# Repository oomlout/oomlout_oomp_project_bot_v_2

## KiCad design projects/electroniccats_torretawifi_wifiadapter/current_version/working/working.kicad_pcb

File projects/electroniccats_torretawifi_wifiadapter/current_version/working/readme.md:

# torretawifi
 
## summary 
* id: electroniccats_torretawifi_wifiadapter
* user: electroniccats
* name: torretawifi
* board: wifiadapter
* repo: https://github.com/ElectronicCats/TorretaWiFi
* src_file_repo_kicad_pcb: ADAPTADORESP/WiFiadapter.kicad_pcb
* src_file_repo_kicad_pcb_link: https://github.com/ElectronicCats/TorretaWiFi/tree/master/ADAPTADORESP/WiFiadapter.kicad_pcb

* src_file_repo_sch: ADAPTADORESP/WiFiadapter.sch
* src_file_repo_sch_link: https://github.com/ElectronicCats/TorretaWiFi/tree/master/ADAPTADORESP/WiFiadapter.sch
* full details link: https://github.com/oomlout/oomlout_oomp_project_bot_v_2/tree/main/projects/electroniccats_torretawifi_wifiadapter/current_version/working

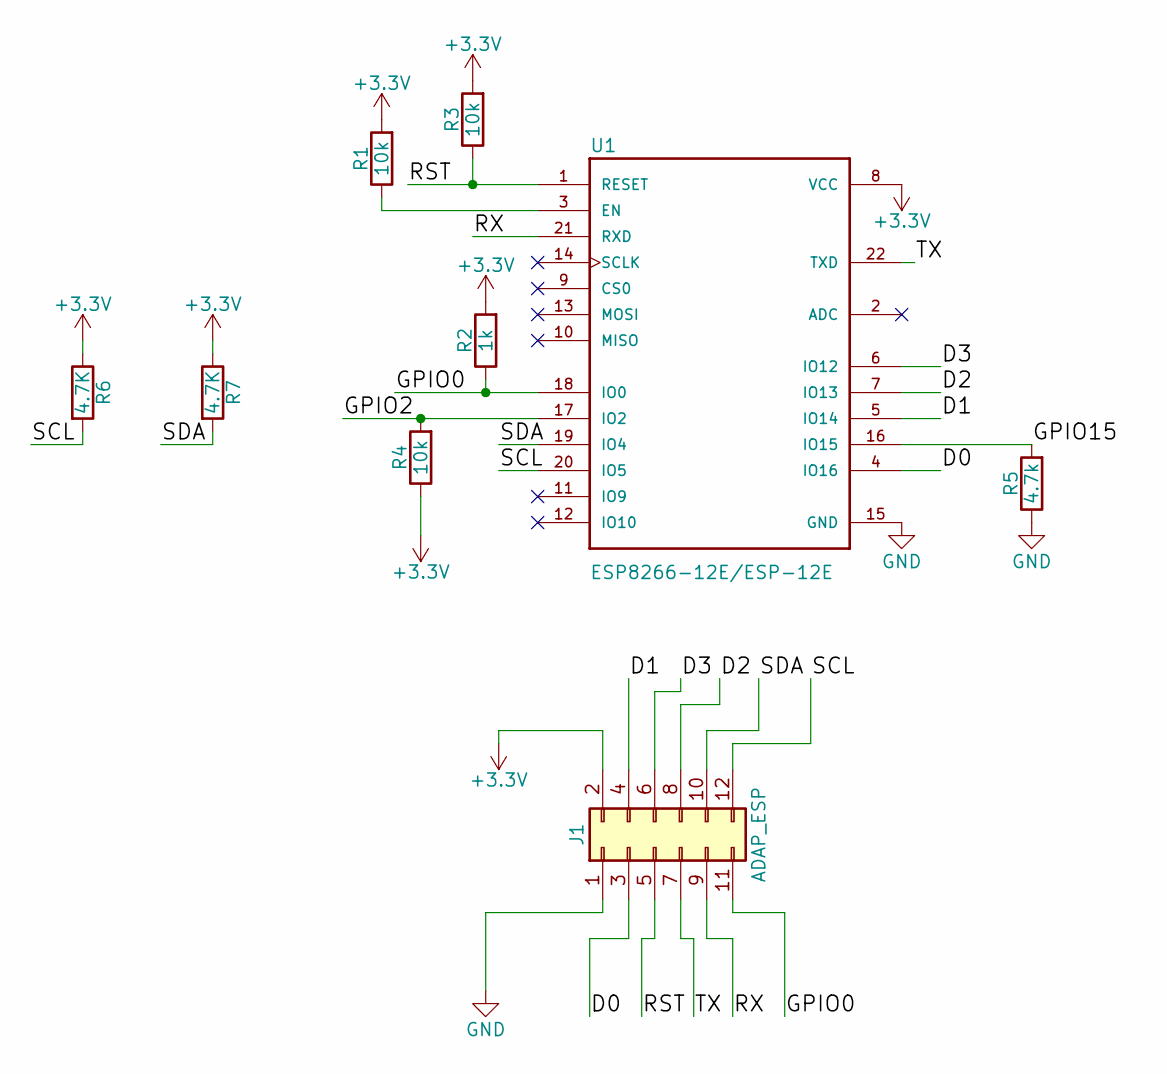
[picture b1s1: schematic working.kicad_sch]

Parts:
J1: ADAP_ESP; Pin_Header_Straight_2x06_Pitch2.54mm
R1, R3, R4: 10k; R_0805_HandSoldering
R2: 1k; R_0805_HandSoldering
R5: 4.7k; R_0805_HandSoldering
R6, R7: 4.7K; R_0805_HandSoldering
U1: ESP8266-12E/ESP-12E; XCVR_ESP8266-12E%2fESP-12E

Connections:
+3V3: J1.2, R1.2, R2.2, R3.2, R4.1, R6.1, R7.1, U1.8 (VCC)
/D0: J1.3, U1.4 (IO16)
/D1: J1.4, U1.5 (IO14)
/D2: J1.8, U1.7 (IO13)
/D3: J1.6, U1.6 (IO12)
/GPIO0: J1.11, R2.1, U1.18 (IO0)
/GPIO2: R4.2, U1.17 (IO2)
/GPIO15: R5.2, U1.16 (IO15)
/RST: J1.5, R3.1, U1.1 (RESET)
/RX: J1.9, U1.21 (RXD)
/SCL: J1.12, R6.2, U1.20 (IO5)
/SDA: J1.10, R7.2, U1.19 (IO4)
/TX: J1.7, U1.22 (TXD)
GND: J1.1, R5.1, U1.15 (GND)
unnamed: R1.1, U1.3 (EN)

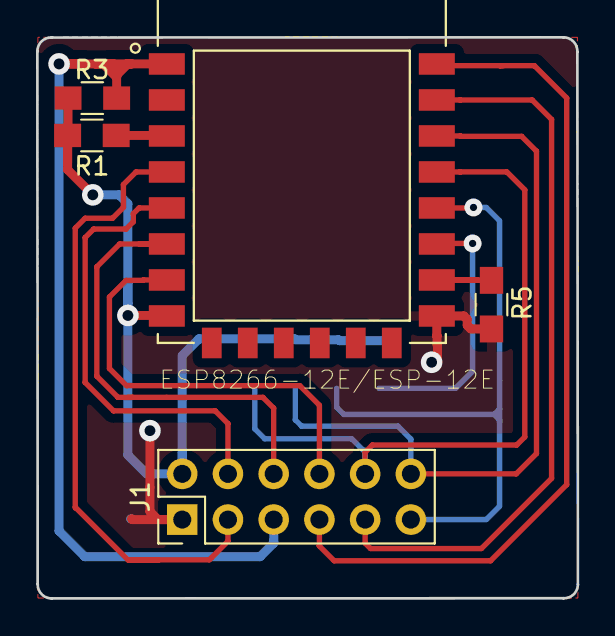
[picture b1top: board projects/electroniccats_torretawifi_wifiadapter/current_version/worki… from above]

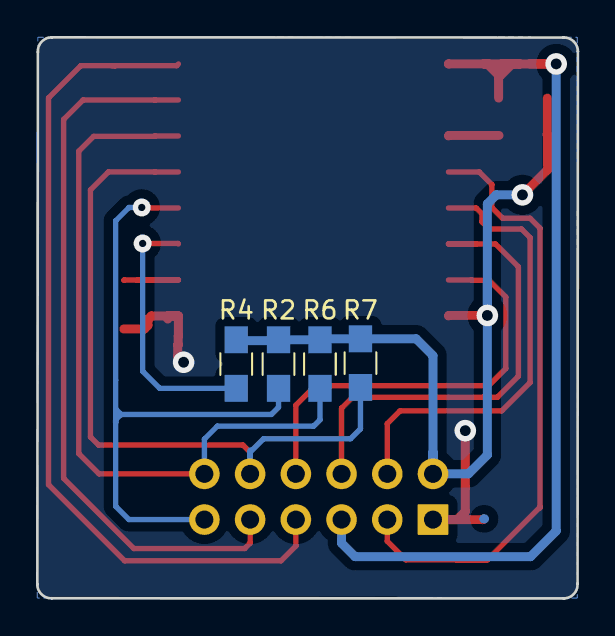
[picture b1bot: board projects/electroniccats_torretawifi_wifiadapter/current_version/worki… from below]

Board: 2 copper layers, 30.0 x 31.2 mm, 9 parts (4 on the bottom side), 15 nets.

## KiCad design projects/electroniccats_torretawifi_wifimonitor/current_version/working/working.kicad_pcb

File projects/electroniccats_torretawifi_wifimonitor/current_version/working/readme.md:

# torretawifi
 
## summary 
* id: electroniccats_torretawifi_wifimonitor
* user: electroniccats
* name: torretawifi
* board: wifimonitor
* repo: https://github.com/ElectronicCats/TorretaWiFi
* src_file_repo_kicad_pcb: Hardware/WiFiMonitor.kicad_pcb
* src_file_repo_kicad_pcb_link: https://github.com/ElectronicCats/TorretaWiFi/tree/master/Hardware/WiFiMonitor.kicad_pcb

* src_file_repo_sch: Hardware/WiFiMonitor.sch
* src_file_repo_sch_link: https://github.com/ElectronicCats/TorretaWiFi/tree/master/Hardware/WiFiMonitor.sch
* full details link: https://github.com/oomlout/oomlout_oomp_project_bot_v_2/tree/main/projects/electroniccats_torretawifi_wifimonitor/current_version/working

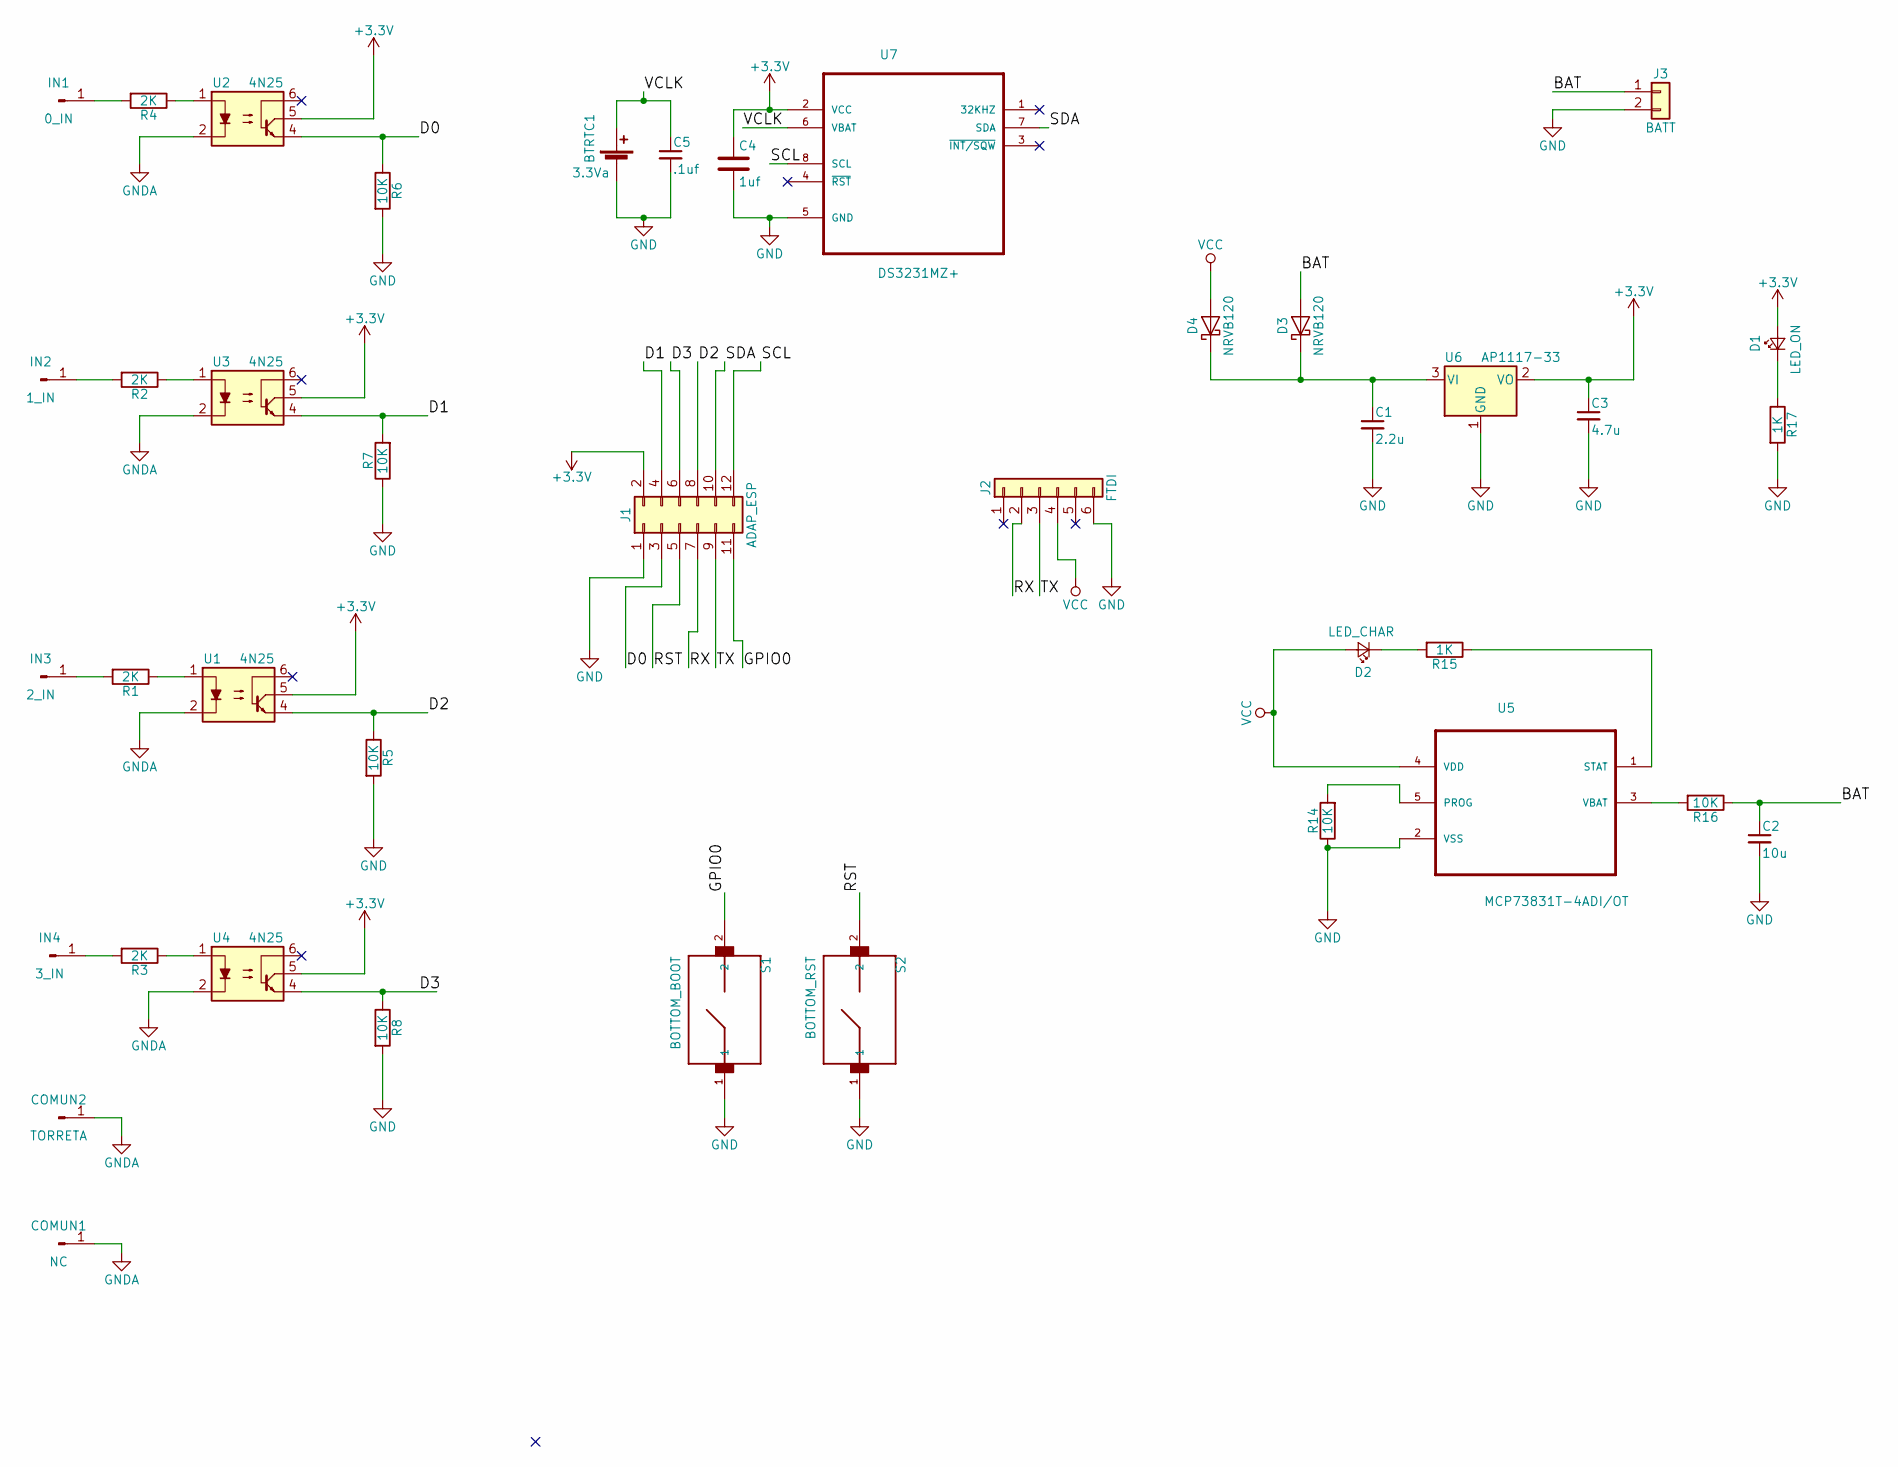
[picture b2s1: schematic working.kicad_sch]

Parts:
BTRTC1: 3.3Va; Keystone_battery_second
C1: 2.2u; C_0805_HandSoldering
C2: 10u; C_0805_HandSoldering
C3: 4.7u; C_0805_HandSoldering
C4: 1uf; C_0805_HandSoldering
C5: .1uf; C_0805_HandSoldering
COMUN1: NC; PAD_5x3mm
COMUN2: TORRETA; PAD_5x3mm
D1: LED_ON; LED_0805_HandSoldering
D2: LED_CHAR; LED_0805_HandSoldering
D3, D4: NRVB120; D_SOD-123
IN1: 0_IN; PAD_5x3mm
IN2: 1_IN; PAD_5x3mm
IN3: 2_IN; PAD_5x3mm
IN4: 3_IN; PAD_5x3mm
J1: ADAP_ESP; Pin_Header_Straight_2x06_Pitch2.54mm
J2: FTDI; Pin_Header_Straight_1x06_Pitch2.54mm
J3: BATT; PINHEAD1-2
R1, R2, R3, R4: 2K; R_0805_HandSoldering
R5, R6, R7, R8, R14, R16: 10K; R_0805_HandSoldering
R15, R17: 1K; R_0805_HandSoldering
S1: BOTTOM_BOOT; SW_B3U-1000P
S2: BOTTOM_RST; SW_B3U-1000P
U1, U2, U3, U4: 4N25; DIP-6_W7.62mm_SMDSocket_SmallPads
U5: MCP73831T-4ADI/OT; SOT95P280X145-5N
U6: AP1117-33; SOT-223-3_TabPin2
U7: DS3231MZ+; SOIC8_150MIL

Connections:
+3V3: C3.1, C4.1, D1.2 (A), J1.2, U1.5, U2.5, U3.5, U4.5, U6.2 (VO), U7.2 (VCC)
/BAT: C2.1, D3.2 (A), J3.1, R16.1
/D0: J1.3, R6.1, U2.4
/D1: J1.4, R7.2, U3.4
/D2: J1.8, R5.1, U1.4
/D3: J1.6, R8.1, U4.4
/GPIO0: J1.11, S1.2
/RST: J1.5, S2.2
/RX: J1.7, J2.2
/SCL: J1.12, U7.8 (SCL)
/SDA: J1.10, U7.7 (SDA)
/TX: J1.9, J2.3
/VCLK: BTRTC1.1 (+), C5.1, U7.6 (VBAT)
GND: BTRTC1.2 (-), C1.2, C2.2, C3.2, C4.2, C5.2, J1.1, J2.6, J3.2, R5.2, R6.2, R7.1, R8.2, R14.1, R17.2, S1.1, S2.1, U5.2 (VSS), U6.1 (GND), U7.5 (GND)
GNDA: COMUN1.1, COMUN2.1, U1.2, U2.2, U3.2, U4.2; also elsewhere on the board
unnamed: C1.1, D3.1 (K), D4.1 (K), U6.3 (VI)
unnamed: D1.1 (K), R17.1
unnamed: D2.1 (K), R15.2
unnamed: IN1.1, R4.2
unnamed: IN2.1, R2.2
unnamed: IN3.1, R1.2
unnamed: IN4.1, R3.2
unnamed: R1.1, U1.1
unnamed: R2.1, U3.1
unnamed: R3.1, U4.1
unnamed: R4.1, U2.1
unnamed: R14.2, U5.5 (PROG)
unnamed: R15.1, U5.1 (STAT)
unnamed: R16.2, U5.3 (VBAT)
VCC: D2.2 (A), D4.2 (A), J2.4, U5.4 (VDD)

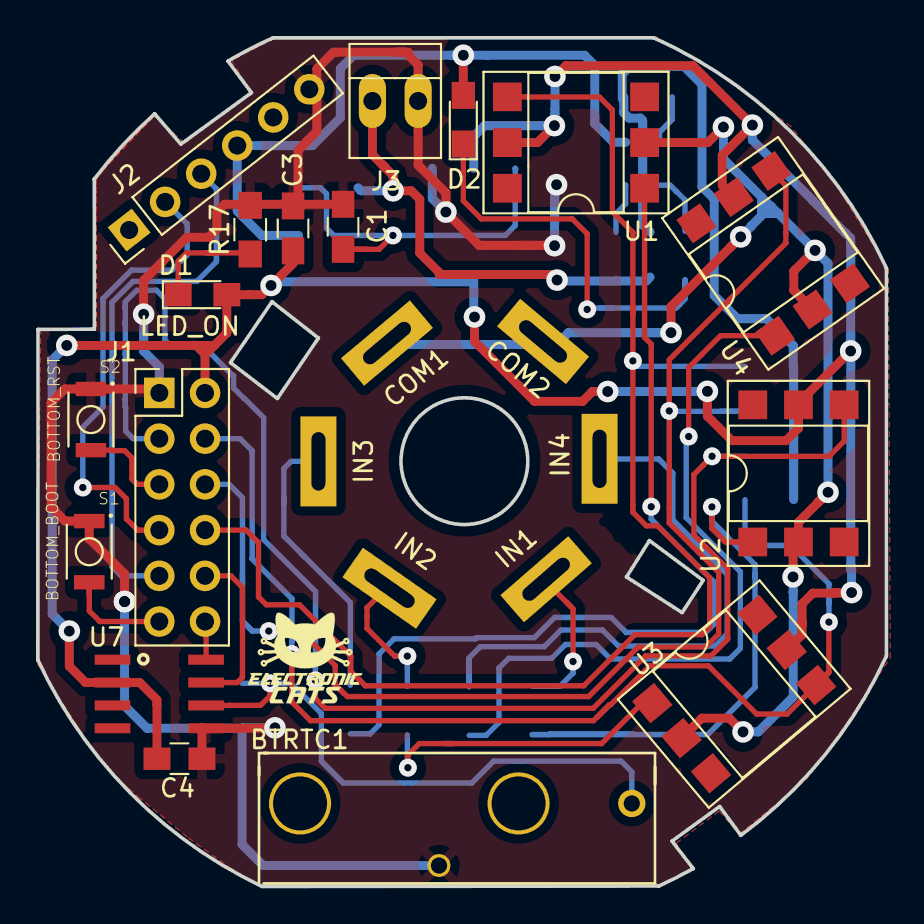
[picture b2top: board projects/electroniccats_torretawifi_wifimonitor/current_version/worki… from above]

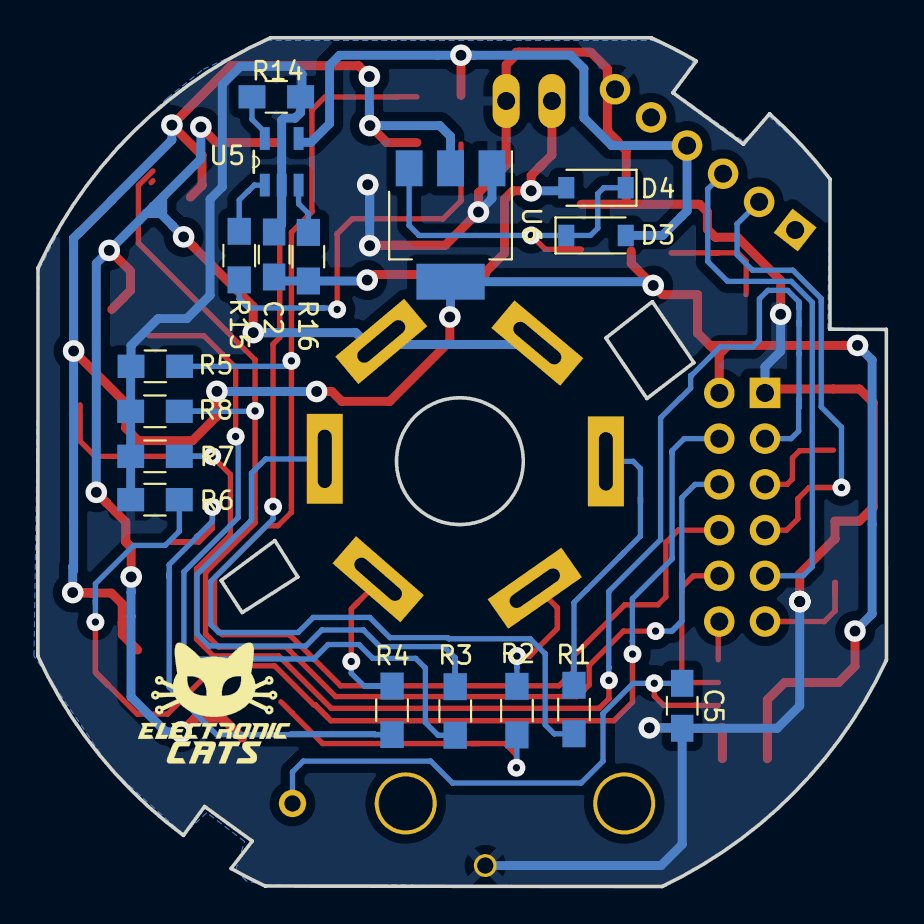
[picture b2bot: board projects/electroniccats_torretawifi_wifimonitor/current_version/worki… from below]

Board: 2 copper layers, 47.2 x 47.1 mm, 40 parts (17 on the bottom side), 30 nets.

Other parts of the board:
COM1: NC; PAD_4X2mmTH
COM2: TORRETA; PAD_4X2mmTH

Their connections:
GNDA: COM1.1, COM2.1; also elsewhere on the board

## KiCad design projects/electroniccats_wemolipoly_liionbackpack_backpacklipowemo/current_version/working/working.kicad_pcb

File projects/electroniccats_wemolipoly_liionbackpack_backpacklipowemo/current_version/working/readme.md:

# wemolipoly_liionbackpack
 
## summary 
* id: electroniccats_wemolipoly_liionbackpack_backpacklipowemo
* user: electroniccats
* name: wemolipoly_liionbackpack
* board: backpacklipowemo
* repo: https://github.com/ElectronicCats/WeMoLiPoly-LiIonBackpack
* src_file_repo_kicad_pcb: BackpackLipoWemo.kicad_pcb
* src_file_repo_kicad_pcb_link: https://github.com/ElectronicCats/WeMoLiPoly-LiIonBackpack/tree/master/BackpackLipoWemo.kicad_pcb

* src_file_repo_sch: BackpackLipoWemo.sch
* src_file_repo_sch_link: https://github.com/ElectronicCats/WeMoLiPoly-LiIonBackpack/tree/master/BackpackLipoWemo.sch
* full details link: https://github.com/oomlout/oomlout_oomp_project_bot_v_2/tree/main/projects/electroniccats_wemolipoly_liionbackpack_backpacklipowemo/current_version/working

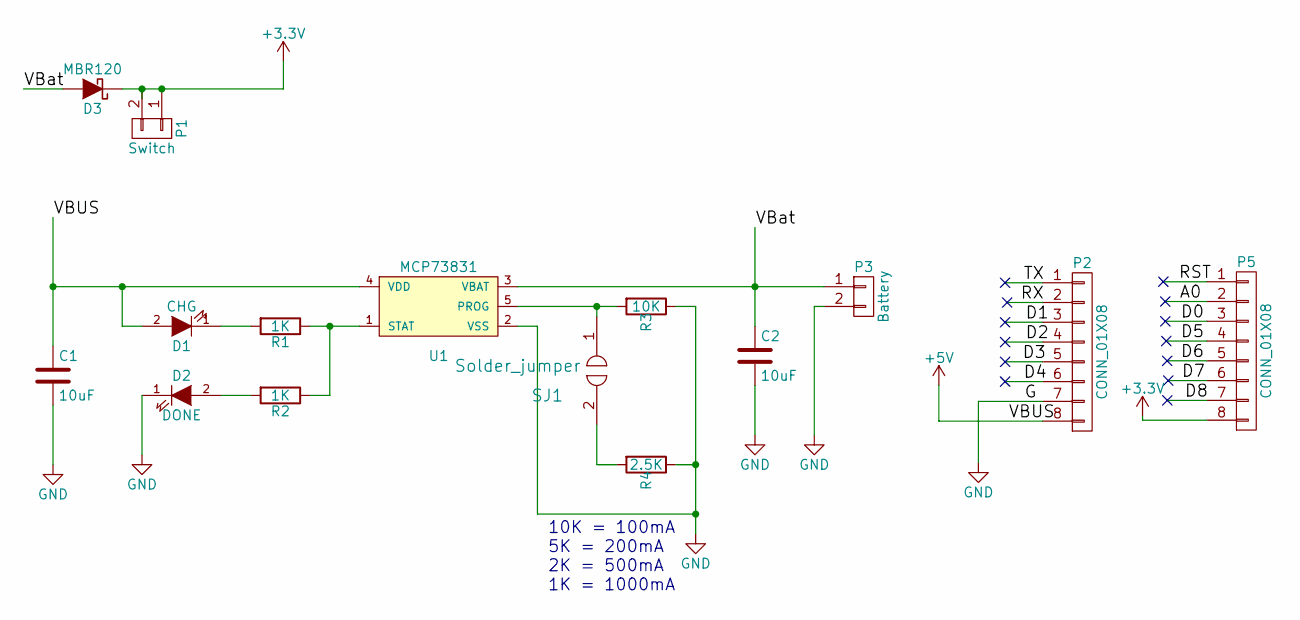
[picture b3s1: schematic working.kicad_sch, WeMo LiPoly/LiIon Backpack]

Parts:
C1, C2: 10uF; C_0603_HandSoldering
D1: CHG; LED-0603
D2: DONE; LED-0603
D3: MBR120; SOD-123
P1: Switch; Pin_Header_Straight_1x02
P2, P5: CONN_01X08; Pin_Header_Straight_1x08
P3: Battery; CONN_JST-2_SMD
R1, R2: 1K; R_0603_HandSoldering
R3: 10K; R_0603_HandSoldering
R4: 2.5K; R_0603_HandSoldering
SJ1: Solder_jumper; S_JUMPER_2
U1: MCP73831; SOT-23-5

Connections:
+3V3: D3.1 (K), P1.1, P1.2, P5.8
+5V: C1.1, D1.2 (A), P2.8, U1.4 (VDD)
/A0: P5.2
/D0: P5.3
/D1: P2.3
/D2: P2.4
/D3: P2.5
/D4: P2.6
/D5: P5.4
/D6: P5.5
/D7: P5.6
/D8: P5.7
/RST: P5.1
/RX: P2.2
/TX: P2.1
/VBat: C2.1, D3.2 (A), P3.1, U1.3 (VBAT)
GND: C1.2, C2.2, D2.1 (K), P2.7, P3.2, R3.1, R4.1, U1.2 (VSS)
unnamed: D1.1 (K), R1.2
unnamed: D2.2 (A), R2.2
unnamed: R1.1, R2.1, U1.1 (STAT)
unnamed: R3.2, SJ1.1, U1.5 (PROG)
unnamed: R4.2, SJ1.2

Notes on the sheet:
10K = 100mA 5K = 200mA 2K = 500mA 1K = 1000mA

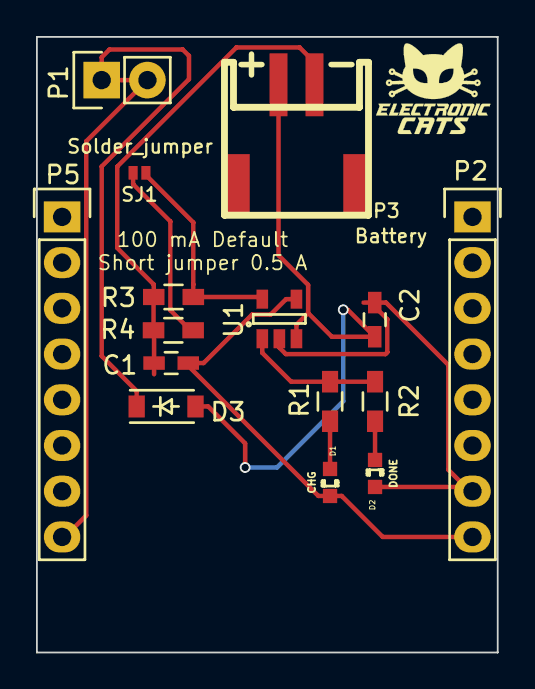
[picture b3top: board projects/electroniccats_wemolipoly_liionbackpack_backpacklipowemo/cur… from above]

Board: 2 copper layers, 25.6 x 34.2 mm, 15 parts (0 on the bottom side), 9 nets.

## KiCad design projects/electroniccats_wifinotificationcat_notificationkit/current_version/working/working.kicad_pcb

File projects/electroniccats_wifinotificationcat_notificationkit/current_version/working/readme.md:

# wifinotificationcat
 
## summary 
* id: electroniccats_wifinotificationcat_notificationkit
* user: electroniccats
* name: wifinotificationcat
* board: notificationkit
* repo: https://github.com/ElectronicCats/WiFiNotificationCat
* src_file_repo_kicad_pcb: NotificationKit.kicad_pcb
* src_file_repo_kicad_pcb_link: https://github.com/ElectronicCats/WiFiNotificationCat/tree/master/NotificationKit.kicad_pcb

* src_file_repo_sch: NotificationKit.sch
* src_file_repo_sch_link: https://github.com/ElectronicCats/WiFiNotificationCat/tree/master/NotificationKit.sch
* full details link: https://github.com/oomlout/oomlout_oomp_project_bot_v_2/tree/main/projects/electroniccats_wifinotificationcat_notificationkit/current_version/working

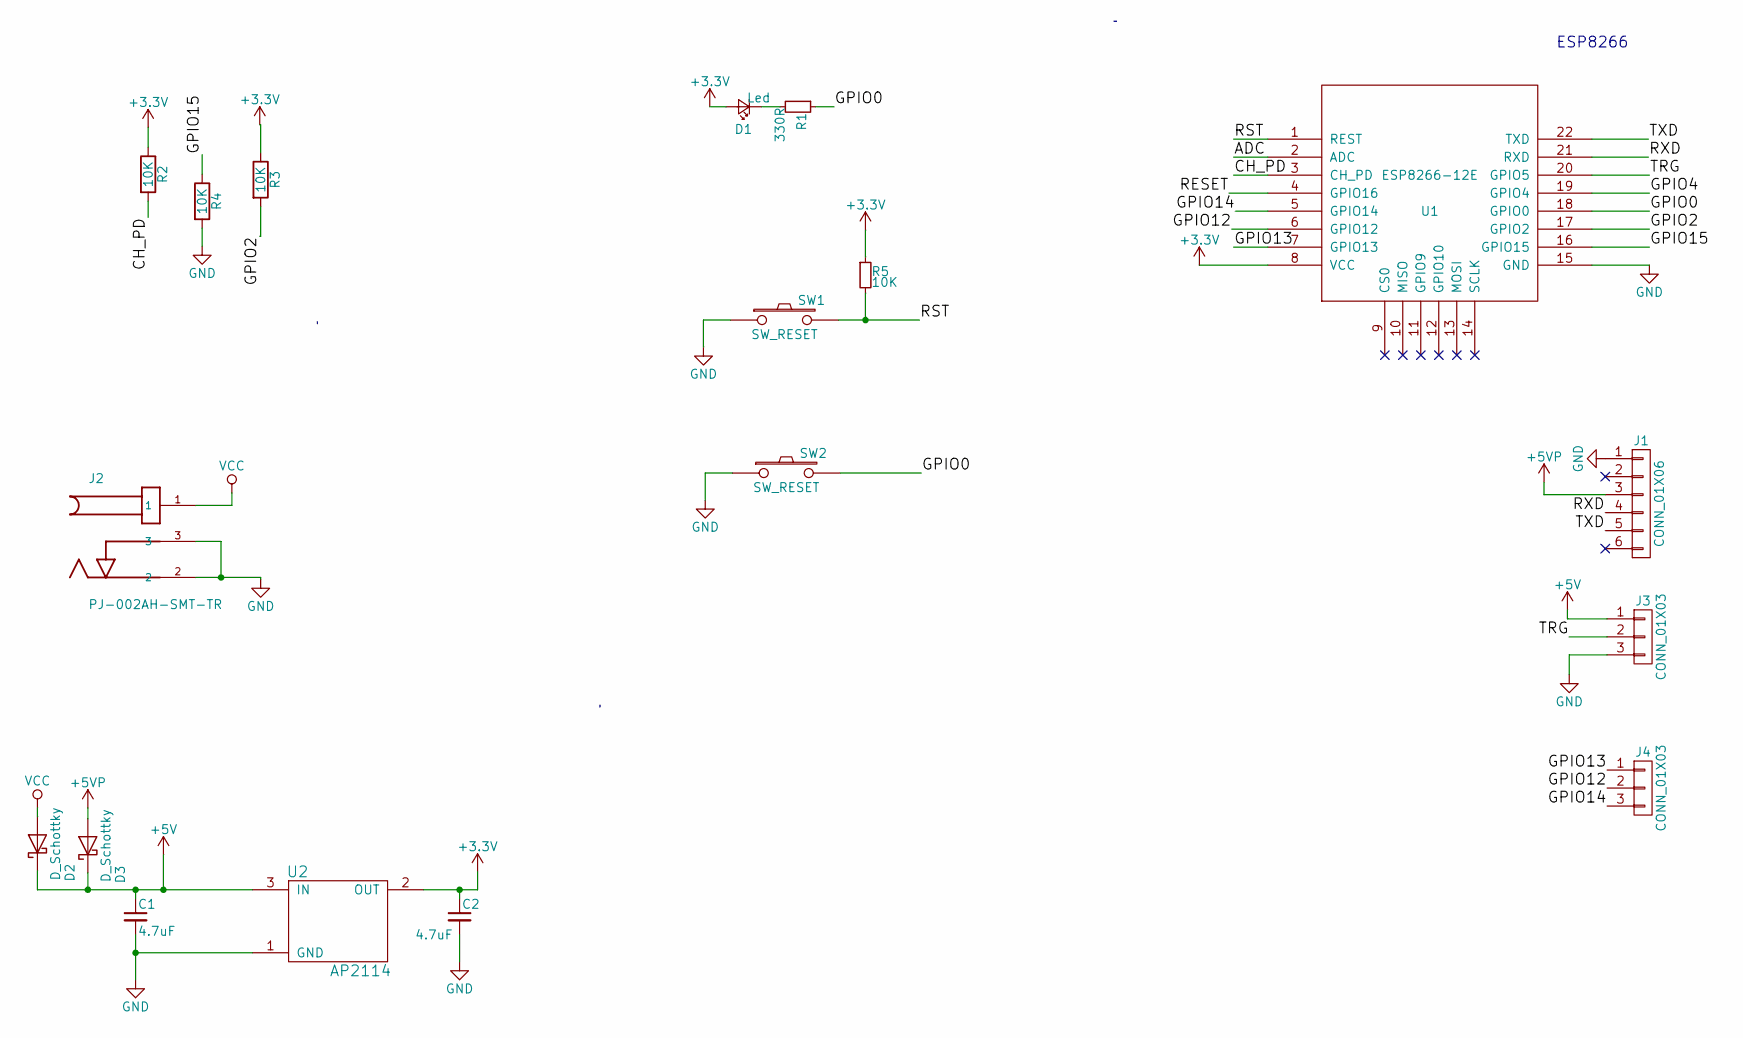
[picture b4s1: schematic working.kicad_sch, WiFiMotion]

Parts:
C1, C2: 4.7uF; C_0805_HandSoldering
D1: Led; LED_0805
D2, D3: D_Schottky; D_SOD-123
J1: CONN_01X06; Pin_Header_Straight_1x06_Pitch2.54mm
J2: PJ-002AH-SMT-TR; CUI-PJ-002AH-SMT_dc-barrel-jack
J3, J4: CONN_01X03; Pin_Header_Straight_1x03_Pitch2.54mm
R1: 330R; R_0805_HandSoldering
R2, R3, R4, R5: 10K; R_0805_HandSoldering
SW1, SW2: SW_RESET; SW_SPST_B3U-1000P
U1: ESP8266-12E; ESP-12E
U2: AP2114; SOT-223-3_TabPin2

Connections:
+3V3: C2.1, D1.2 (A), R2.1, R3.1, R5.1, U1.8 (VCC), U2.2 (OUT)
+5V: C1.1, D2.1 (K), D3.1 (K), J3.1, U2.3 (IN)
+5VP: D3.2 (A), J1.3
/ADC: U1.2 (ADC)
/CH_PD: R2.2, U1.3 (CH_PD)
/GPIO0: R1.1, SW2.2, U1.18 (GPIO0)
/GPIO2: R3.2, U1.17 (GPIO2)
/GPIO4: U1.19 (GPIO4)
/GPIO12: J4.2, U1.6 (GPIO12)
/GPIO13: J4.1, U1.7 (GPIO13)
/GPIO14: J4.3, U1.5 (GPIO14)
/GPIO15: R4.1, U1.16 (GPIO15)
/RESET: U1.4 (GPIO16)
/RST: R5.2, SW1.2, U1.1 (REST)
/RXD: J1.4, U1.21 (RXD)
/TRG: J3.2, U1.20 (GPIO5)
/TXD: J1.5, U1.22 (TXD)
GND: C1.2, C2.2, J1.1, J2.2, J2.3, J3.3, R4.2, SW1.1, SW2.1, U1.15 (GND), U2.1 (GND)
unnamed: D1.1 (K), R1.2
VCC: D2.2 (A), J2.1

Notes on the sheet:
ESP8266

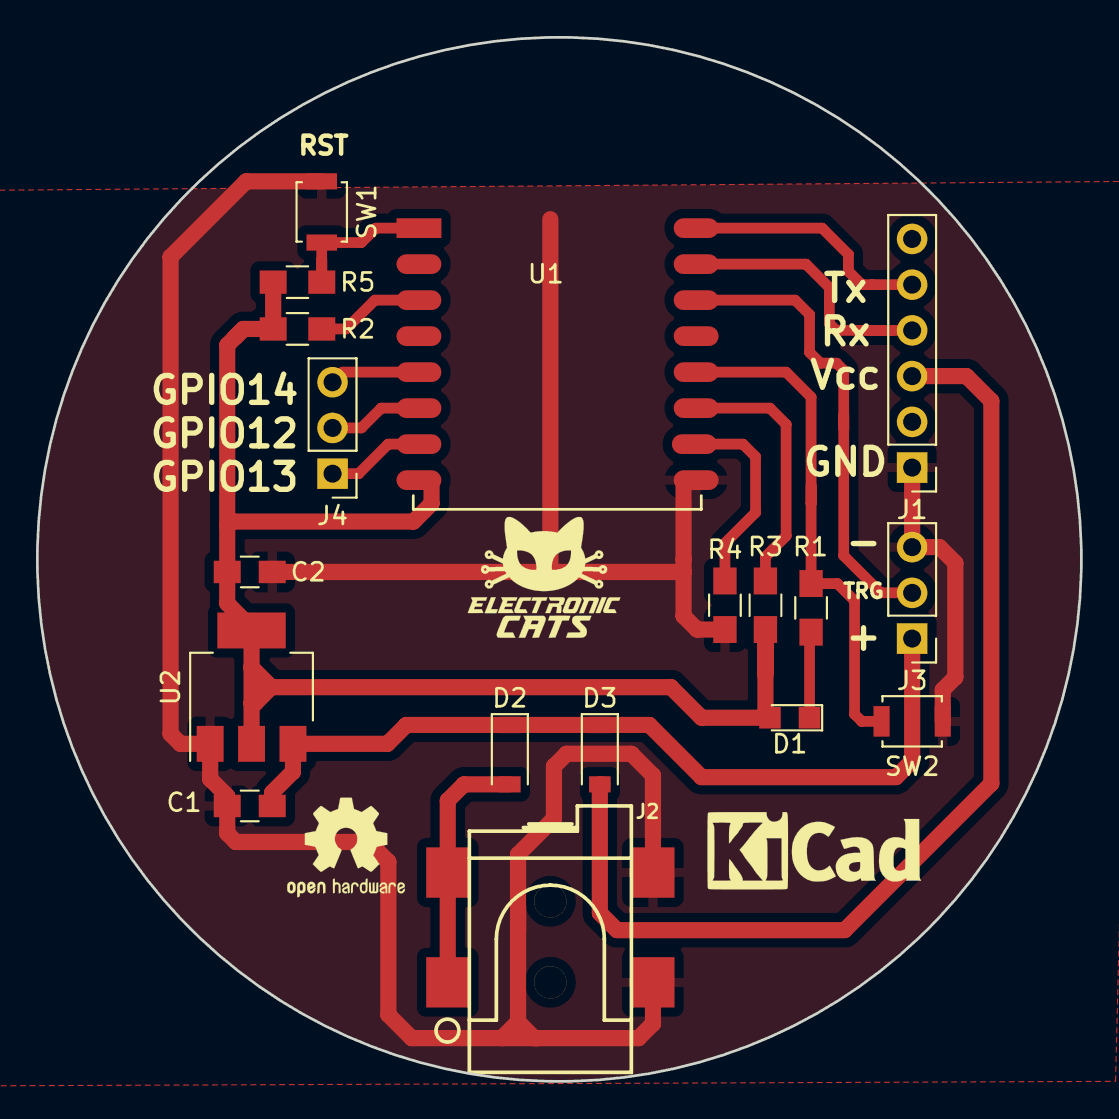
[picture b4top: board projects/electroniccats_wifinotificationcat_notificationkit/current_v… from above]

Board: 2 copper layers, 58.0 x 58.0 mm, 18 parts (0 on the bottom side), 17 nets.

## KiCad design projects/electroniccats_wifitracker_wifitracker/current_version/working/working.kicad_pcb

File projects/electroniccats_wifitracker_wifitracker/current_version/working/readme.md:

# wifitracker
 
## summary 
* id: electroniccats_wifitracker_wifitracker
* user: electroniccats
* name: wifitracker
* board: wifitracker
* repo: https://github.com/ElectronicCats/WiFiTracker
* src_file_repo_kicad_pcb: WiFiTracker.kicad_pcb
* src_file_repo_kicad_pcb_link: https://github.com/ElectronicCats/WiFiTracker/tree/master/WiFiTracker.kicad_pcb

* src_file_repo_sch: WiFiTracker.sch
* src_file_repo_sch_link: https://github.com/ElectronicCats/WiFiTracker/tree/master/WiFiTracker.sch
* full details link: https://github.com/oomlout/oomlout_oomp_project_bot_v_2/tree/main/projects/electroniccats_wifitracker_wifitracker/current_version/working

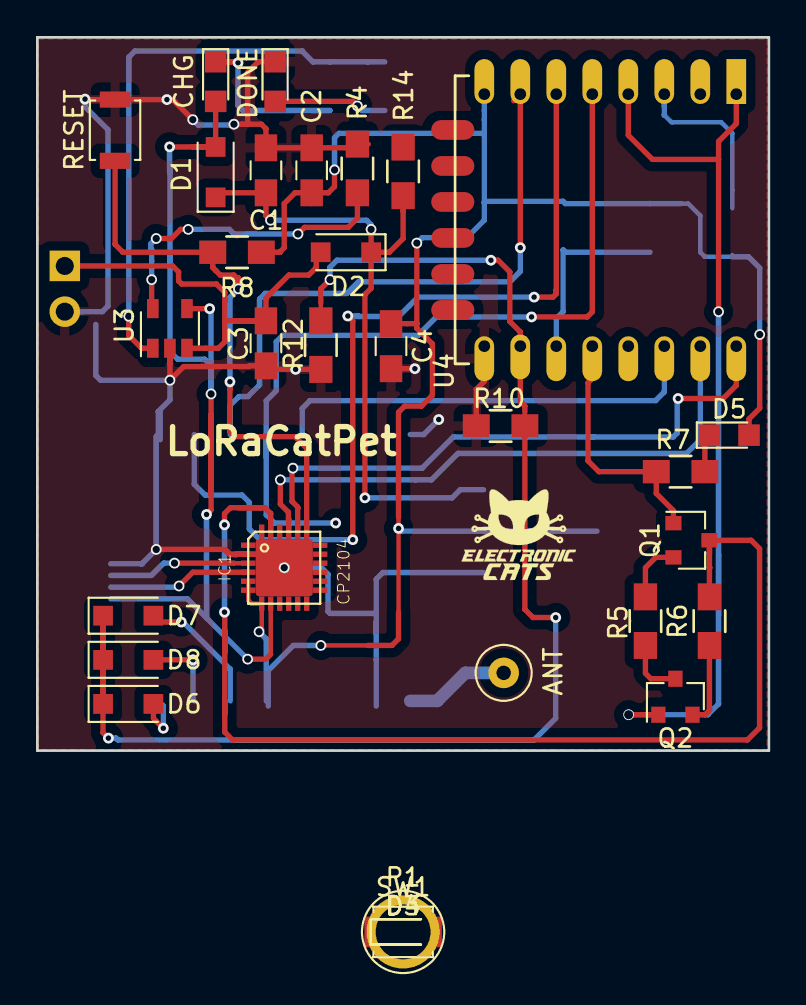
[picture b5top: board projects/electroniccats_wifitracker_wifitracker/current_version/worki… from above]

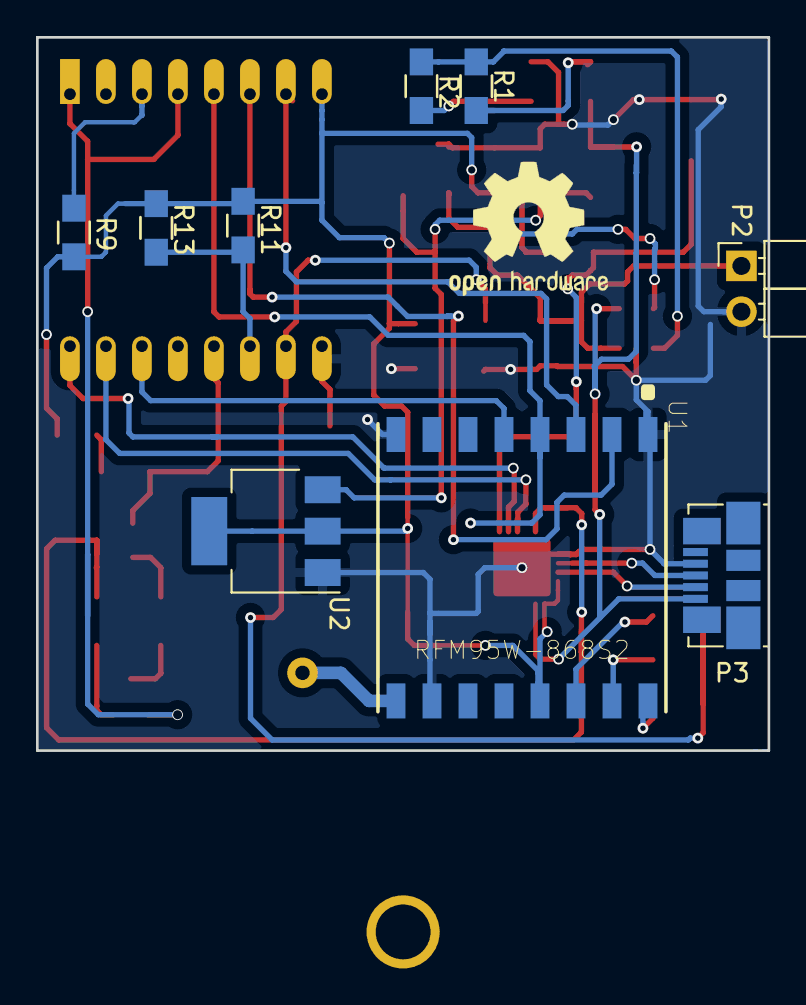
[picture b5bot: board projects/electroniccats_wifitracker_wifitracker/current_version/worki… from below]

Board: 2 copper layers, 40.6 x 39.6 mm, 40 parts (9 on the bottom side), 31 nets.

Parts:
ANT: ANT; 1pin
C1, C2: 4.7uF; C_0805_HandSoldering
C3, C4: 10uF; C_0805_HandSoldering
CHG: CHG; LED_0805
D1, D2: D_Schottky; D_SOD-123F
D3: CHG; LED_0805
D4: DONE; LED_0805
D5: Led; LED_0805
D6, D7, D8: D; D_SOD-123F
DONE: DONE; LED_0805
IC1: CP2104; QFN24-PAD
P1: ANT; 1pin
P2: Battery; Pin_Header_Angled_1x02_Pitch2.54mm
P3: USB_B; USB_Micro-B_Molex_47346-0001
Q1, Q2: MMBT2222A; SOT-23
R1, R2, R7: 330R; R_0805_HandSoldering
R4, R5, R6, R8, R9, R10, R11, R12, R13, R14: 10K; R_0805_HandSoldering
RESET: SW_RESET; SW_SPST_B3U-1000P
SW1: SW_RESET; SW_SPST_B3U-1000P
U1: RFM95W-868S2; XCVR_RFM95W-868S2
U2: AP2114; SOT-223-3Lead_TabPin2
U3: MCP73831T-2ATI/OT; SOT-23-5
U4: ESP8266-12E; ESP-12E

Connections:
+3V3: C2.1, C4.1, D5.2, IC1.5, IC1.6, IC1.7, R8.1, R9.1, R11.1, R13.1, U1.13, U2.2, U4.8
+BATT: C3.1, D2.2, P2.1, U3.3
/CH_PD: R9.2, U4.3
/DIO0: D7.2, U1.14
/DIO1: D8.2, U1.15
/DIO2: D6.2, U1.16
/DTR: IC1.23, Q1.3, R6.2
/GPIO0: Q1.1, R7.1, U4.18
/GPIO2: R11.2, R13.2, U4.17
/GPIO5: U1.5, U4.20
/GPIO12: U1.2, U4.6
/GPIO13: U1.3, U4.7
/GPIO14: U1.4, U4.5
/GPIO15: D6.1, D7.1, D8.1, R10.1, R12.1, U4.16
/RESET: Q2.1, R8.2, SW1.2, U4.1, U4.4
/RTS: IC1.19, Q2.3, R5.2
/RXD: IC1.21, U4.21
/TXD: IC1.20, U4.22
GND: C1.2, C2.2, C3.2, C4.2, D4.1, DONE.1, IC1.2, IC1.TP, P2.2, P3.4, R4.2, R10.2, R12.2, RESET.1, SW1.1, U1.1, U1.8, U1.10, U2.1, U3.2, U4.15
unnamed: C1.1, D1.1, D2.1, R14.2, U2.3
unnamed: CHG.1, D3.1, R1.2
unnamed: D4.2, DONE.2, R2.2
unnamed: D5.1, R7.2
unnamed: IC1.3, P3.3
unnamed: IC1.4, P3.2
unnamed: ANT.1, P1.1, U1.9
unnamed: Q1.2, R5.1
unnamed: Q2.2, R6.1
unnamed: R1.1, R2.1, U3.1
unnamed: R4.1, U3.5
VCC: CHG.2, D1.2, D3.2, IC1.8, P3.1, U3.4

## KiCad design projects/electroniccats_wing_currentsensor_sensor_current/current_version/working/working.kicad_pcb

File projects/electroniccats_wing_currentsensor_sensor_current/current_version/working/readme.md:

# wing_currentsensor
 
## summary 
* id: electroniccats_wing_currentsensor_sensor_current
* user: electroniccats
* name: wing_currentsensor
* board: sensor_current
* repo: https://github.com/ElectronicCats/Wing_CurrentSensor
* src_file_repo_kicad_pcb: sensor_current.kicad_pcb
* src_file_repo_kicad_pcb_link: https://github.com/ElectronicCats/Wing_CurrentSensor/tree/main/sensor_current.kicad_pcb

* src_file_repo_sch: sensor_current.sch
* src_file_repo_sch_link: https://github.com/ElectronicCats/Wing_CurrentSensor/tree/main/sensor_current.sch
* full details link: https://github.com/oomlout/oomlout_oomp_project_bot_v_2/tree/main/projects/electroniccats_wing_currentsensor_sensor_current/current_version/working

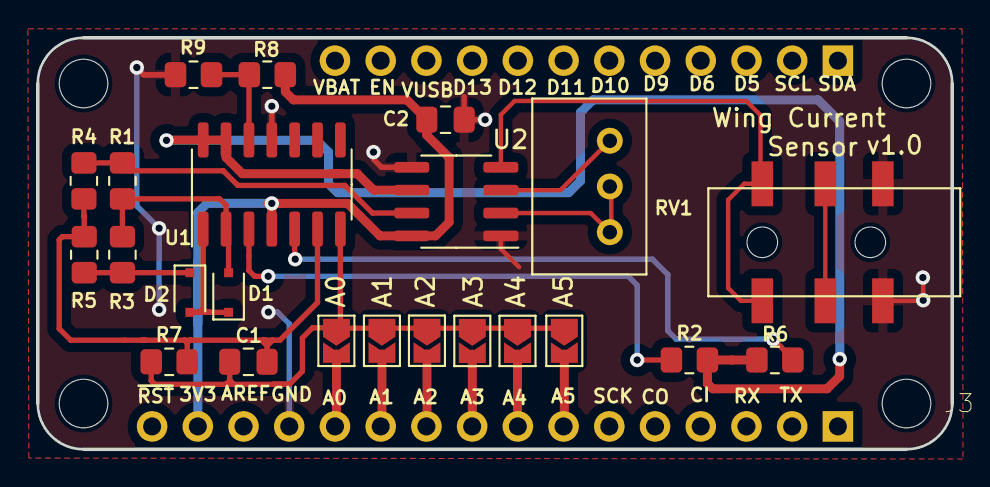
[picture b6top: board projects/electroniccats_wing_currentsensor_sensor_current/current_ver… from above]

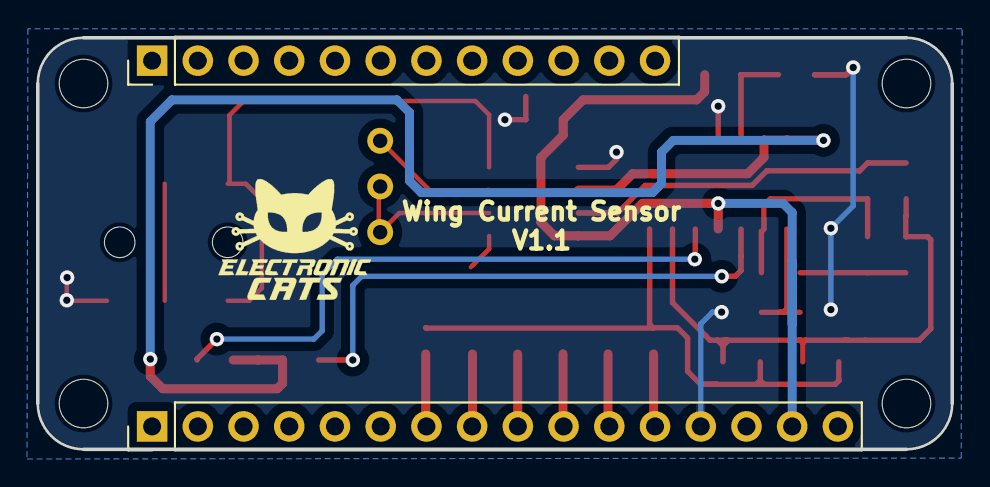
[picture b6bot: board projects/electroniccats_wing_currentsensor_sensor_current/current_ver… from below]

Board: 2 copper layers, 50.8 x 22.9 mm, 25 parts (2 on the bottom side), 21 nets.

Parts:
A0: A0; SolderJumper-2_P1.3mm_Open_TrianglePad1.0x1.5mm
A1: A1; SolderJumper-2_P1.3mm_Open_TrianglePad1.0x1.5mm
A2: A2; SolderJumper-2_P1.3mm_Open_TrianglePad1.0x1.5mm
A3: A3; SolderJumper-2_P1.3mm_Open_TrianglePad1.0x1.5mm
A4: A4; SolderJumper-2_P1.3mm_Open_TrianglePad1.0x1.5mm
A5: A5; SolderJumper-2_P1.3mm_Open_TrianglePad1.0x1.5mm
C1: 10 μ; C_0805_2012Metric_Pad1.18x1.45mm_HandSolder
C2: 0.1μ; C_0805_2012Metric_Pad1.18x1.45mm_HandSolder
D1, D2: DIODE; D_SOD-323F
J1: feather long; PinHeader_1x16_P2.54mm_Vertical
J2: feather short; PinHeader_1x12_P2.54mm_Vertical
J3: PJ-320B; CUI_SJ-3524-SMT
R1, R3, R4, R7, R8, R9: 10K; R_0805_2012Metric_Pad1.20x1.40mm_HandSolder
R2, R5: 5K; R_0805_2012Metric_Pad1.20x1.40mm_HandSolder
R6: 3.3K; R_0805_2012Metric_Pad1.20x1.40mm_HandSolder
RV1: 10K; Potentiometer_Bourns_3299W_Vertical
U1: TL084; SO-14_3.9x8.65mm_P1.27mm
U2: AD8226; SOIC-8_3.9x4.9mm_P1.27mm

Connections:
+3V3: C2.1, J1.15, R8.1, U1.4, U2.8
/A0: A0.2, J1.12
/A1: A1.2, J1.11
/A2: A2.2, J1.10
/A3: A3.2, J1.9
/A4: A4.2, J1.8
/A5: A5.2, J1.7
/IN+: J3.3, U2.4
/OUT: A0.1, A1.1, A2.1, A3.1, A4.1, A5.1, C1.1, R7.1, U1.7
/OUT1: R1.1, R4.1, U2.7
/VREF: R2.2, R6.2, U1.13, U1.14, U2.6
GND: C2.2, J1.13, J3.1, R9.2, U1.11, U2.1, U2.5
unnamed: C1.2, R4.2, R5.2, R7.2, U1.6
unnamed: D1.1, D2.2, U1.1
unnamed: D1.2, R1.2, R3.1, U1.2
unnamed: D2.1, R3.2, R5.1
unnamed: R2.1, U1.3
unnamed: R6.1, U1.5
unnamed: R8.2, R9.1, U1.12
unnamed: RV1.1, RV1.2, U2.2
unnamed: RV1.3, U2.3
